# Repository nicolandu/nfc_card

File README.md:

# nfc_card
This is an adaptation of the OnBoard jam with my own antenna. It is designed in KiCad, with this plugin:
[https://github.com/Neurotech-Hub/KiCad-Plugins-8.0](https://github.com/Neurotech-Hub/KiCad-Plugins-8.0).

I also designed a simple enclosure, which is to be printed out of TPU for a bit of edge protection to add
the card to a keyring. Due to the cost of the PCB and the assembly, I plan to keep the board and to tap
it to transmit my contact info, rather than necessarily handing out the contraption.

See [https://cad.onshape.com/documents/652e3e97175898963abc7477/w/3581c96ca1af5364a35a6b2c/e/11e05677b8a6fddd2746e93f](https://cad.onshape.com/documents/652e3e97175898963abc7477/w/3581c96ca1af5364a35a6b2c/e/11e05677b8a6fddd2746e93f) for
the housing's design files.

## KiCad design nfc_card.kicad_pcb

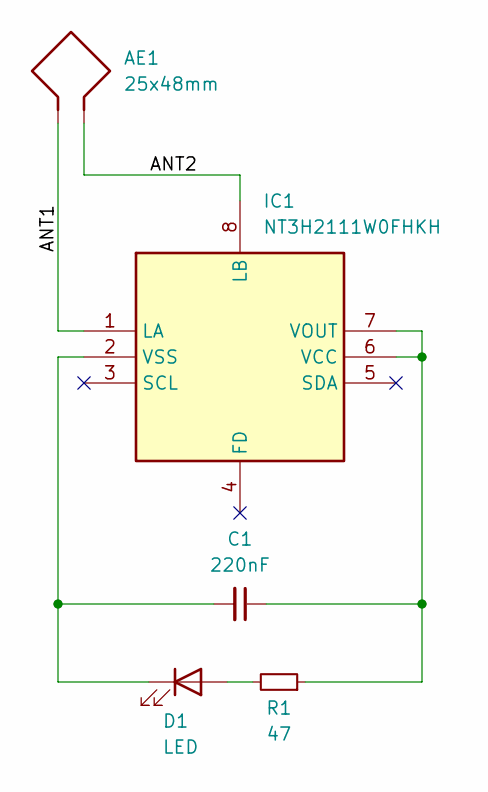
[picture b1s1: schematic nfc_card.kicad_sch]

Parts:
AE1: 25x48mm; Antenna_25x48mm
C1: 220nF; C_0402_1005Metric
D1: LED; LED_0805_2012Metric
IC1: NT3H2111W0FHKH; QFN50P160X160X50-8N; Mouser Part Number 771-NT3H2111W0FHKH
R1: 47; R_0402_1005Metric

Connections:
/ANT1: AE1.1, IC1.1 (LA)
/ANT2: AE1.2, IC1.8 (LB)
unnamed: D1.2 (A), R1.2
unnamed: C1.2, D1.1 (K), IC1.2 (VSS)
unnamed: C1.1, IC1.6 (VCC), IC1.7 (VOUT), R1.1

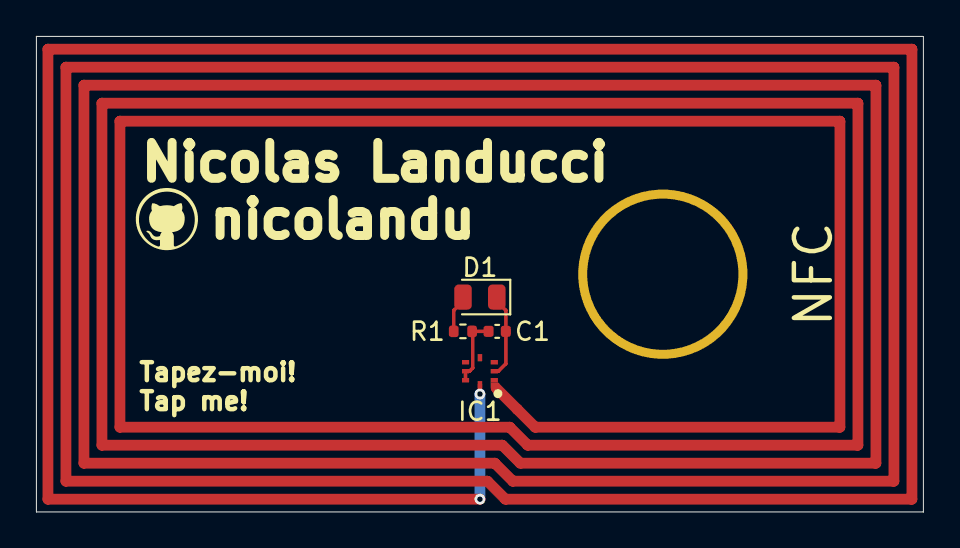
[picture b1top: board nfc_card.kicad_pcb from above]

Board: 2 copper layers, 49.3 x 26.4 mm, 5 parts (0 on the bottom side), 5 nets.

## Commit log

2024-07-24 Initial commit
    Add gitignore
    Create LICENSE
2024-07-24 Start schematic
2024-07-24 Add antenna
2024-07-24 Finish wiring
2024-07-24 Add housing export files
